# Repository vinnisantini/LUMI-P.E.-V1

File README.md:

# LUMI P.E. V1
LUMI Pocket Edition, keychain flashlight

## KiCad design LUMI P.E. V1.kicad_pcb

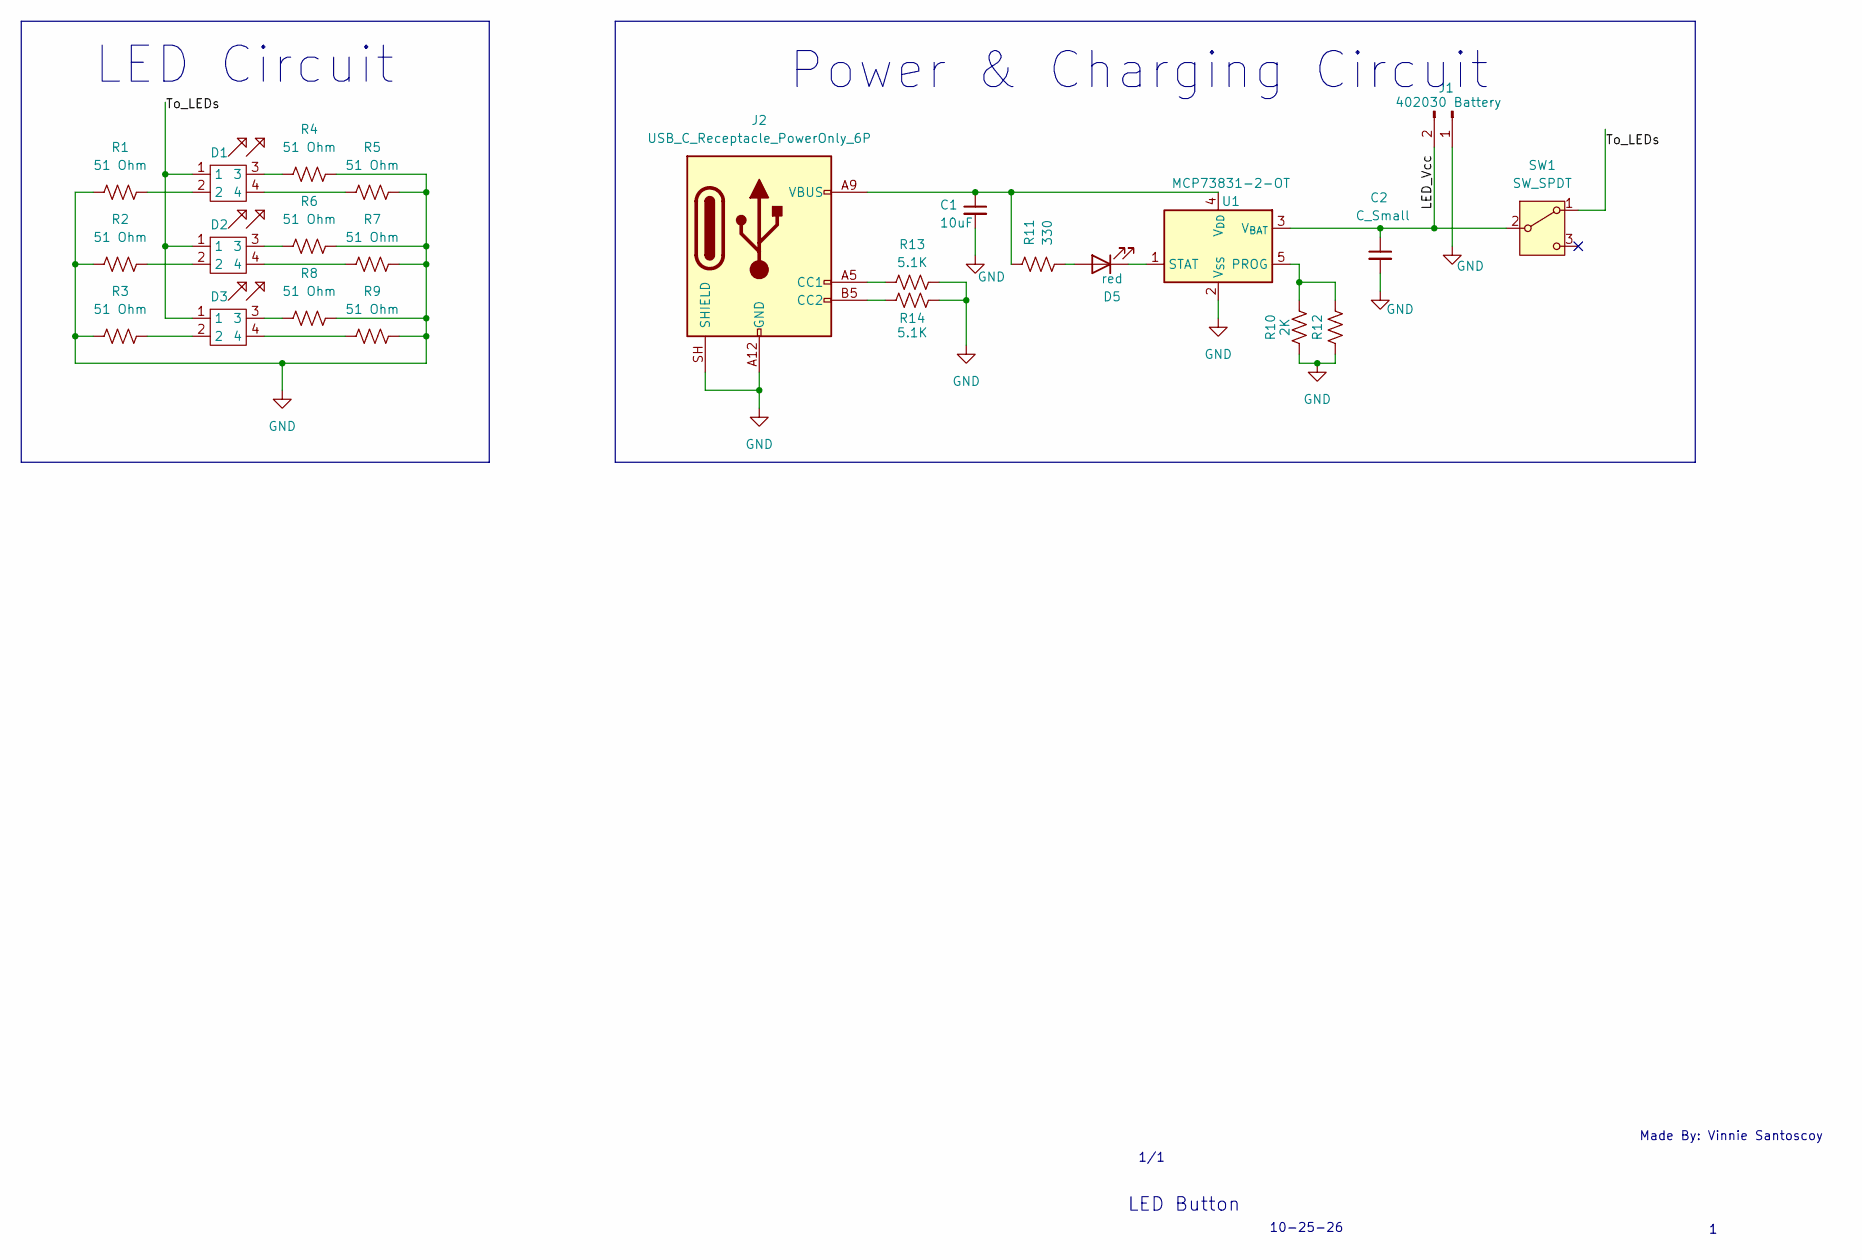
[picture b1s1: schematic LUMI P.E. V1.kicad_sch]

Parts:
C1: 10uF; C_0603_1608Metric
C2: C_Small; C_0603_1608Metric
D1, D2, D3: LED_QBLP677AD-IWD-2897
D5: red; LED_0603_1608Metric
J1: 402030 Battery; PinHeader_1x02_P2.54mm_Vertical
J2: USB_C_Receptacle_PowerOnly_6P; USB_C_Receptacle_GCT_USB4135-GF-A_6P_TopMnt_Horizontal
R1, R2, R3, R4, R5, R6, R7, R8, R9: 51 Ohm; R_0603_1608Metric
R10: 2K; R_0603_1608Metric
R11: 330; R_0603_1608Metric
R12: R_0603_1608Metric
R13, R14: 5.1K; R_0603_1608Metric
SW1: SW_SPDT; SW_SPDT_PCM12
U1: MCP73831-2-OT; SOT-23-5

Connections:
/LED_Vcc: C2.1, J1.2, SW1.2 (B), U1.3 (V_{BAT})
/To_LEDs: D1.1, D2.1, D3.1, SW1.1 (A)
GND: C1.2, C2.2, J1.1, J2.A12 (GND), J2.B12 (GND), J2.SH (SHIELD), R1.1, R2.1, R3.1, R4.2, R5.2, R6.2, R7.2, R8.2, R9.2, R10.1, R12.2, R13.2, R14.2, U1.2 (V_{SS})
unnamed: D1.2, R1.2
unnamed: D1.3, R4.1
unnamed: D1.4, R5.1
unnamed: D2.2, R2.2
unnamed: D2.3, R6.1
unnamed: D2.4, R7.1
unnamed: D3.2, R3.2
unnamed: D3.3, R8.1
unnamed: D3.4, R9.1
unnamed: D5.2 (A), R11.1
unnamed: D5.1 (K), U1.1 (STAT)
unnamed: J2.A5 (CC1), R13.1
unnamed: J2.B5 (CC2), R14.1
unnamed: R10.2, R12.1, U1.5 (PROG)
unnamed: C1.1, J2.A9 (VBUS), J2.B9 (VBUS), R11.2, U1.4 (V_{DD})

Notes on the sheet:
10-25-26
Made By: Vinnie Santoscoy
LED Button
LED Circuit
1/1
Power & Charging Circuit

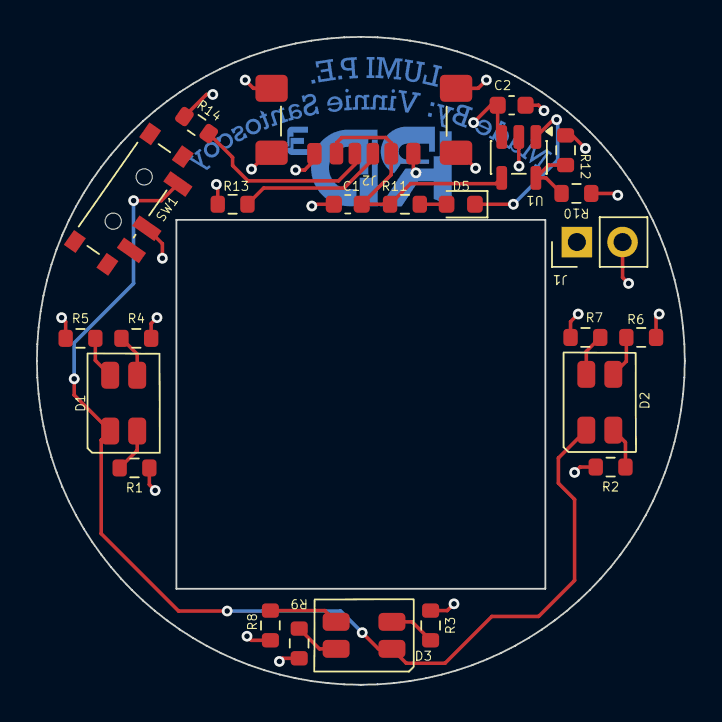
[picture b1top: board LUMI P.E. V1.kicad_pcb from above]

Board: 4 copper layers, 36.0 x 36.0 mm, 24 parts (0 on the bottom side), 18 nets.
